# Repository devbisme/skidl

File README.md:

<div align="center">
  
</div>

**Never use a lousy schematic editor again!**

SKiDL is a Python package that lets you describe electronic circuits using code instead of schematic editors. Write your circuit as a Python program, and SKiDL outputs a netlist for PCB layout tools. It's "infrastructure as code" for electronics.

* Free software: MIT license
* Documentation: http://devbisme.github.io/skidl
* User Forum: https://github.com/devbisme/skidl/discussions

## Why SKiDL?

**Text-Based Circuit Design** `git`, `diff`, branching, and code review work on it like any other source.

**Compact & Powerful**: Describe complex circuits in a fraction of the space. No more tracing signals across multi-page schematics.

**Hierarchical Design**: Mix linear, hierarchical, and modular design approaches as needed.

**Reusable Design**: Share circuit modules on PyPI and GitHub. Create parametric "smart" circuits that adapt based on requirements.

**Design Automation**: Build circuits algorithmically. Generate repetitive structures, automatically size components, and create design variants programmatically.

**Electrical Rules Checking**: Catch common mistakes like unconnected pins, drive conflicts, and power connection errors.

**One Description, Many Outputs** Generate netlists, XML BOMs, DOT graphs, or a placed-and-routed schematic — as editable KiCad files or as static, hyperlinked SVG (KiCad 6–10) — from the same source. KiCad today; other backends can be added.

**Python Ecosystem**: Leverage Python's vast ecosystem for simulation, analysis, documentation, and automation.

## Quick Example

Here's a simple voltage divider that demonstrates SKiDL's syntax:

```python
from skidl import *

# Create input & output voltages and ground reference
vin, vout, gnd = Net('VI'), Net('VO'), Net('GND')

# Create two resistors with values and footprints
r1, r2 = 2 * Part("Device", 'R', dest=TEMPLATE, footprint='Resistor_SMD.pretty:R_0805_2012Metric')
r1.value, r2.value = '1K', '500'

# Connect the circuit elements.
vin & r1 & vout & r2 & gnd

# Or connect pin-by-pin if you prefer
# vin += r1[1]
# vout += r1[2], r2[1] 
# gnd += r2[2]

# Check for errors and generate netlist
ERC()
generate_netlist(tool=KICAD10)
```

For a more complex example, here's a two-input AND gate built from discrete transistors:

```python
from skidl import *

# Create part templates
q = Part("Transistor_BJT", "Q_PNP_CBE", dest=TEMPLATE)
r = Part("Device", "R", dest=TEMPLATE)

# Create nets
gnd, vcc = Net("GND"), Net("VCC")
a, b, a_and_b = Net("A"), Net("B"), Net("A_AND_B")

# Instantiate parts
gndt = Part("power", "GND")             # Ground terminal
vcct = Part("power", "VCC")             # Power terminal
q1, q2 = q(2)                           # Two transistors
r1, r2, r3, r4, r5 = r(5, value="10K")  # Five 10K resistors

# Make connections - notice the readable topology
a & r1 & q1["B C"] & r4 & q2["B C"] & a_and_b & r5 & gnd
b & r2 & q1["B"]
q1["C"] & r3 & gnd
vcc += q1["E"], q2["E"], vcct
gnd += gndt

generate_netlist(tool=KICAD10)
```

## Advanced Features

**Hierarchical design.** Nest subcircuits to build large systems from blocks; the hierarchy carries through to the generated net lists and schematics.

**Part and net classes.** Attach design rules, manufacturing requirements, and electrical specs to sets of parts or nets.

**Smart Part Libraries**: Search parts by function, automatically assign footprints, and access any KiCad library.

**Multiple Output Formats**: Generate netlists for KiCad, XML for BOMs, or go directly to PCB layout.

**Visual Output**: Create editable KiCad schematic files or static SVG drawings of them (KiCad 6–10), or DOT graphs for documentation. Hierarchical designs become linked SVG pages you can click through.

**SPICE Integration**: Run simulations directly on your SKiDL circuits.

## Installation

```bash
pip install skidl
```

Set up KiCad library access (optional but recommended):

```bash
# Linux/Mac
export KICAD_SYMBOL_DIR="/usr/share/kicad/symbols"

# Windows  
set KICAD_SYMBOL_DIR=C:\Program Files\KiCad\share\kicad\symbols
```

## Getting Started

1. **Learn the basics**: Check out the [documentation](http://devbisme.github.io/skidl) for comprehensive tutorials
2. **Try examples**: Explore the `tests/examples/` directory in the repository
3. **Get help**: Join discussions in our [user forum](https://github.com/devbisme/skidl/discussions)
4. **Convert existing designs**: Use the `netlist_to_skidl` tool to convert KiCad designs to SKiDL

## Troubleshooting

### "No libraries found" or symbol resolution errors

SKiDL needs to know where your KiCad symbol libraries are. If `KICAD_SYMBOL_DIR` is not
set or points to the wrong path, parts won't resolve.

**Find your KiCad symbol library path:**

```bash
# Linux (package manager install)
ls /usr/share/kicad/symbols/

# Linux (Flatpak)
ls /var/lib/flatpak/app/org.kicad.KiCad/current/active/files/share/kicad/symbols/

# macOS (Homebrew)
ls /Applications/KiCad/KiCad.app/Contents/SharedSupport/symbols/

# Windows (typical)
dir "C:\Program Files\KiCad\8.0\share\kicad\symbols"
```

**Set the environment variable:**

```bash
# Linux/macOS — add to ~/.bashrc, ~/.zshrc, or ~/.zprofile
export KICAD_SYMBOL_DIR="/usr/share/kicad/symbols"

# Windows PowerShell
[System.Environment]::SetEnvironmentVariable("KICAD_SYMBOL_DIR", "C:\Program Files\KiCad\8.0\share\kicad\symbols", "User")
```

**Verify it works:**

```bash
python -c "from skidl import Part; r = Part('Device', 'R'); print(f'Found: {r.name}')"
```

### KiCad version compatibility

SKiDL supports KiCad 5 through 10. The exceptions are the two drawing outputs —
`generate_schematic()` and `generate_svg()` — which require KiCad 6 or later.
KiCad 5 uses the legacy EESCHEMA `.sch` format, which is no longer written, and its
libraries don't carry the symbol graphics the SVG renderer draws from. KiCad 5
netlists, PCBs, and XML BOMs are unaffected.

If you see parsing errors with newer KiCad library
files, make sure you're running the latest version of SKiDL:

```bash
pip install --upgrade skidl
```

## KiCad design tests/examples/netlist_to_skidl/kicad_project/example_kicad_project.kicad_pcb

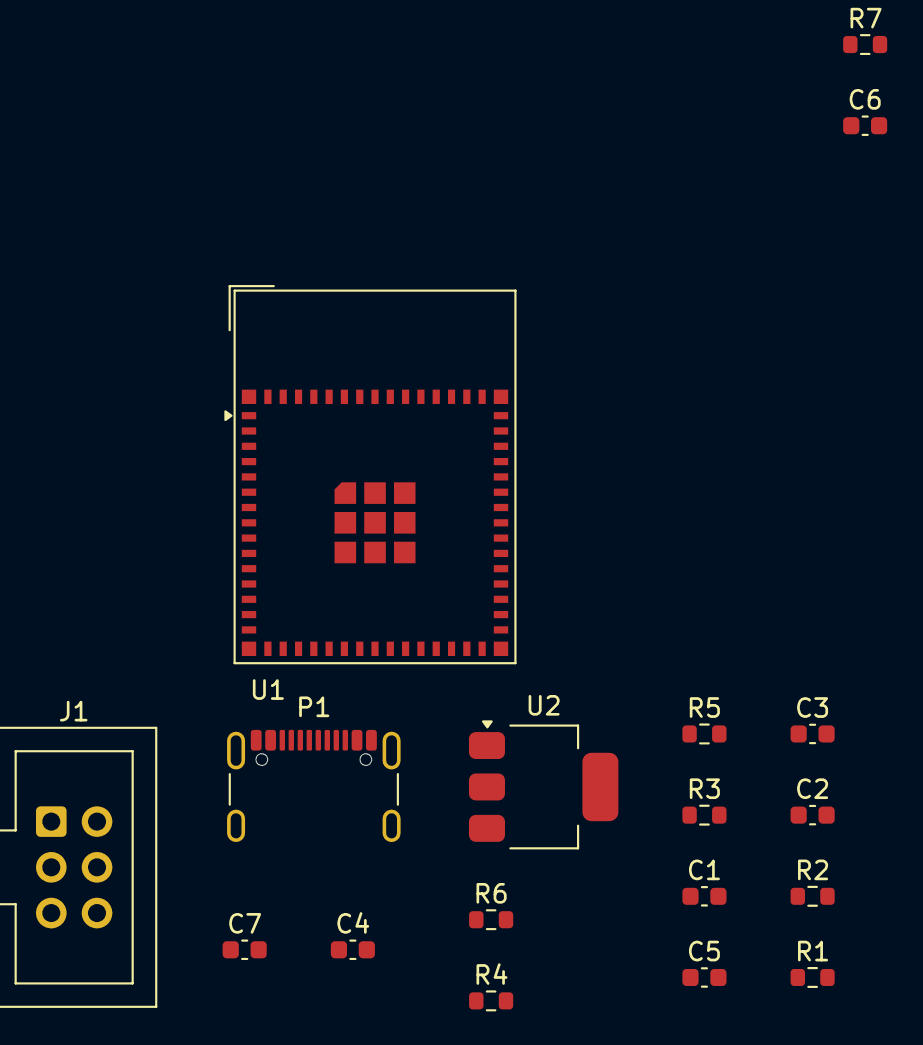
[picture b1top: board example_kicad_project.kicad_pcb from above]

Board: 2 copper layers, 18 parts (0 on the bottom side), 13 nets, no tracks yet.

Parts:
C1, C3, C4, C7: 10uF; C_0603_1608Metric
C2, C5, C6: 100nF; C_0603_1608Metric
J1: Conn_02x03_Odd_Even; IDC-Header_2x03_P2.54mm_Vertical
P1: USB_C_Plug_USB2.0; USB_C_Receptacle_GCT_USB4105-xx-A_16P_TopMnt_Horizontal
R1, R4, R5: 1k; R_0603_1608Metric
R2, R3, R6: 2k; R_0603_1608Metric
R7: 5.1K; R_0603_1608Metric
U1: ESP32-S3-MINI-1; ESP32-S2-MINI-1
U2: NCP1117-3.3_SOT223; SOT-223-3_TabPin2

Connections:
3v3_monitor: C5.1, R4.1, R6.2, U1.6
5v_monitor: C6.1, R3.2, R5.1, U1.7
+3V3: C1.1, C3.1, J1.2, R2.1, R6.1, U1.3, U2.2
+5V: C4.1, C7.1, P1.A4, P1.A9, P1.B4, P1.B9, R3.1, U2.3
D+: P1.A6, U1.24
D-: P1.A7, U1.23
GND: C1.2, C2.2, C3.2, C4.2, C5.2, C6.2, C7.2, J1.4, P1.A1, P1.A12, P1.B1, P1.B12, P1.S1, R1.2, R4.2, R5.2, R7.2, U1.1, U1.2, U1.42, U1.43, U1.46, U1.47, U1.48, U1.49, U1.50, U1.51, U1.52, U1.53, U1.54, U1.55, U1.56, U1.57, U1.58, U1.59, U1.60, U1.61, U1.62, U1.63, U1.64, U1.65, U2.1
unnamed: P1.A5, R7.1
esp32s3mini1/EN: J1.1, U1.45
esp32s3mini1/HW_VER: C2.1, R1.1, R2.2, U1.5
esp32s3mini1/IO0: J1.6, U1.4
esp32s3mini1/RX: J1.5, U1.40
esp32s3mini1/TX: J1.3, U1.39

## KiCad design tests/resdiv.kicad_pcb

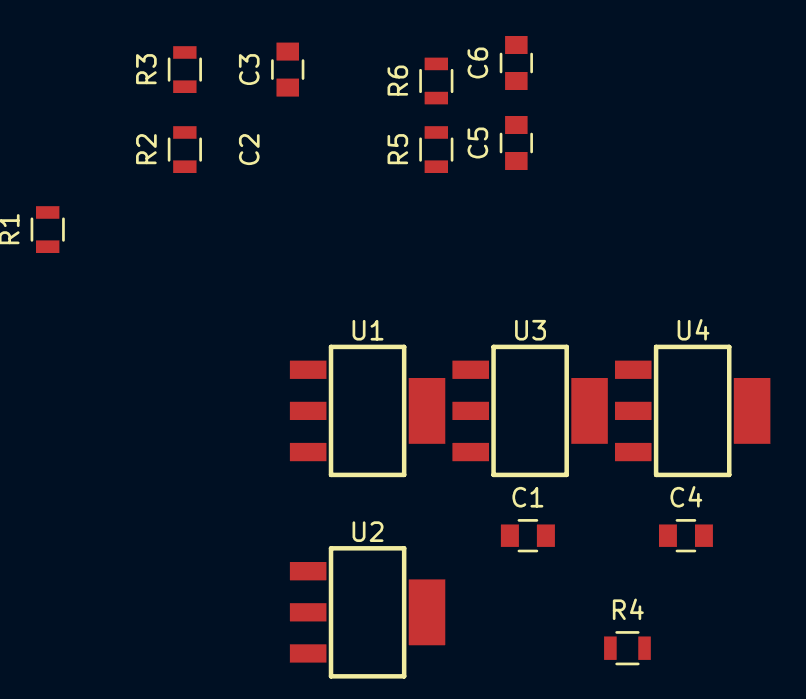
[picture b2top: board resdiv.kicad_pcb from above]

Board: 2 copper layers, 16 parts (0 on the bottom side), 4 nets, no tracks yet.

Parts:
C1, C4: C-NONPOL; C_0805
C2, C5: 1uF; C_0805
C3, C6: 2uF; C_0805
R1, R4: R; R_0805
R2, R5: 1K6; R_0805
R3, R6: 500K3; R_0805
U1, U2, U3, U4: NCV1117; SOT-223

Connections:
A: C2.1, R2.1, U1.3, U2.3
B: C2.2, C3.1, C5.1, R2.2, R3.1, R5.1, U1.2, U2.2, U3.3, U4.3
GND: C3.2, C6.2, R3.2, R6.2, U1.1, U2.1, U3.1, U4.1
unnamed: C5.2, C6.1, R5.2, R6.1, U3.2, U4.2

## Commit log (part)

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2025-06-01 Use a stack for managing the entrance and exit of Circuit objects called within another Circuit object.
2025-06-03 SchNode is no longer a subclass of Node. They should be kept separate at this point.
2025-06-08 Enhance get_unique_name function to handle numeric suffixes more effectively by appending underscores and optimizing name conflict resolution.
2025-06-08 Removed completed TODO comment for reworking get_unique_name function
2025-06-08 Enhance get_skidl_trace function documentation and improve call stack filtering of calls to SKiDL package functions.
2025-06-08 Removed old code that was commented out.
2025-06-14 Added import of setup_function and teardown_function otherwise initialization and termination of the tests won't be done.
2025-06-21 SKiDL no longer runs under Python 3.7 because it uses Simp_sexp.
2025-06-21 bare_warnings and bare_errors are now added to the total warning and error counts.
2025-06-21 Add tag management to SkidlBaseObj so it would apply to nodes and parts.
2025-06-21 Cleaned-up Node handling including checking Node tags.
2025-06-21 Import HIER_SEP from schbaseobj.py instead of circuit.py.
2025-06-21 Remove tag handling from Part since that is now provided in SkidlBaseObj.
2025-06-22 Add support for tracking absolute or relative source file paths in gen_netlist functions
2025-06-23 Refactor gen_sheetpath and gen_sheetpath_tstamp to create their outputs with the same format as KiCad.
2025-06-30 Replace dependency on kinparse with simp_sexp.
2025-06-30 Updated example projected to KiCad 9.
2025-07-02 Replaced many .format() calls with f-strings.
2025-07-03 Add examples and test data to the repo.
2025-07-05 Add testing with Python 3.6.
2025-07-13 Enhance net class management in SKiDL
    - Updated the netclass.py module to provide comprehensive net class management features, including detailed documentation, examples, and improved functionality for defining and managing net classes.
    - Introduced a new NetClassList class for managing multiple NetClass objects, supporting automatic deduplication and circuit-aware lookups.
    - Modified the NetClass constructor to ensure default priority assignment and improved error handling.
    - Updated unit tests to validate the new net class merging behavior and ensure correct propagation of net class attributes across merged nets.
2025-07-13 Add priority sorting for elements in a NetClass and corresponding unit test
2025-07-13 Add netclass handling to netlist generation and default netclass assignment
2025-07-13 Add netclass handling to netlist generation for KiCad 8 and assign Default netclass to all nets
2025-07-14 Add PartClass and PartClassList for managing part classes in Part objects
2025-07-15 Added AI-generated tests of the Circuit class.
2025-07-15 Add NCNet class import for enhanced net management
2025-07-19 Remove NCNet import from __init__.py because normal SKiDL users don't need it.
2025-07-20 Insert part classes into netlist output.
2025-07-20 Replace Group with SubCircuit which now can serve as a class and a decorator for creating hierarchical circuits. Retain Group for backward compatibility.
2025-07-20 - Correct __all__. - Add documentation.
2025-07-24 Rename 'i_expression' and 'v_expression' to 'current_expression' and 'voltage_expression' in the PySpice keyword translation table.
2025-07-28 Give notice along with corrective action if SPICE simulation cannot be performed.
2025-08-03 Add tests for net classes.
2025-08-03 Refactor add_netclass and add_partclass methods to accept multiple classes and add property accessors for netclasses and partclasses.
2025-08-03 Preliminary update of HISTORY for version 2.1.0
2025-08-03 Refactor part copying logic to handle iterable attributes correctly and remove unnecessary part class list copying.
2025-08-04 Fix copy method in Parameters class to return a Parameters instance instead of a dict
2025-08-04 Add hiernodes property to return the chain of hierarchical nodes for a SKiDL object.
2025-08-04 Add test for hierarchical part classes.
2025-08-05 Remove UTF-8 encoding setup for Python 2 compatibility
2025-08-07 Add test for hierarchical net classes.
2025-08-09 Update return type in SubCircuit class documentation to reflect Node object
2025-08-10 Merged subcircuit handling from subcircuit.py into Node objects.
2025-08-10 Update check for power to support PartClassList in Net objects.
2025-08-10 Add AI-generated unit tests for PartClass, PartClassList, NetClass, and NetClassList functionality
2025-08-14 - Replaced DesignClass with NetClassList and PartClassList. - Fixed hierarchical propagation of net and part classes.
2025-08-14 Refactor tests to use updated PartClass and NetClass implementations.
2025-08-14 Updated history.
2025-08-16 Fix formatting in Net class docstring for clarity
2025-08-16 - Link buses to the nodes where they were instantiated. - Link nodes to the buses where they were instantiated.
2025-08-16 Add tests for net classes in buses.
2025-08-16 Added instructions for creating llms.txt file.
2025-08-17 Refactor file path search for footprint library table retrieval.
2025-08-17 Add interactive mode support to scriptinfo function so it returns "skidl_REPL" as the script name.
2025-08-20 When generating a unique name for a name ending with a digit, append an underscore before searching the heap so previous generated names will be found.
2025-08-21 Remove "_lib" from backup library name assignment and use script name directly with appended "_sklib.py".
2025-08-23 Improve Bus and Net copy method to include circuit and name attributes.
2025-08-23 Replaced hierarchical_name with hiername in Part class.
2025-08-24 Moved hiertuple, hierpath, etc. from SkidlBaseObj to Part and Node classes.
2025-08-28 - Replace hiername with hiertuple. - Add hiertuple property to Part and PartUnit.
2025-08-28 Update xfail annotations to include PlacementFailure for schematic generation tests
2025-08-28 Add missing libraries for testing schematic geneation under KiCad 5.
2025-08-29 Add generate_dot function to SKiDL module and export it in __all__
2025-08-29 Remove unused schematic example files for and gate and landing example
2025-08-30 Update default tool selection to KICAD9 in pytest setup_function.
2025-08-30 Add AI-generated tests based on examples from landing.md documentation.
2025-08-30 Replaced README.rst file with README.md markdown file.
2025-08-30 Bump version to 2.1.0 and update release date
2025-08-30 Added llms files generated by llms-txt.io.
2025-08-31 Converted Restructured text files to Markdown.
2025-08-31 Rewrite of README.
2025-08-31 Added blog posts on 2.1.0 release and SKiDL cheatsheet.
2025-09-01 Combined testing for all Python versions, KiCad versions, SPICE, and schematics into a single testenv.
2025-09-01 Rebuilt docs to include corrected cheatsheet.
2025-09-01 Fixed link to cheatsheet in blog post preview.
2025-09-04 Removed 'spice' from the envlist in tox.ini
2025-09-04 Correct XSPICE unit test.
2025-09-07 Add os.path.abspath() to expand_path() utility.
2025-09-07 Add __iter__ to SchLib to enable iterating over the parts in a library.
2025-09-10 - SKiDL configuration now uses standard locations for storing .skidlcfg. - Configuration process now creates a storage directory for pickled part libraries and the part search database. - Use collect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
2025-09-11 - Updated configuration of unit tests to use a .skidlcfg file. - Updated test of part search to account for new database search technique.
2025-09-13 Added skidl-part-search command-line utility.
2025-09-14 Corrected version number.
2025-09-16 Reset file name assignment to the base name of the library. Complete file path is now stored in the filepath attribute.
2025-09-20 Add interactive search mode with command history support.
2025-09-20 - Enhance search output with colored number of results message. - Correct readline history bindings.
2025-09-20 Improve interactive browsing experience with enhanced part navigation and display features
2025-09-27 Separated pin handling in Part into a mixin class.
2025-09-28 - Add create_pins() for adding pins to Parts and SubCircuits. - Add erc_desc() to SubCircuit for reporting ERC warnings/errors. - Add PinMixin to SubCircuit class. - Move match_pin_regex property fro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
2025-09-28 Remove --pdb option from pytest command in tox.ini
2025-10-04 Bus indexing using aliases is now supported.
2025-10-05 Add test for nested subcircuits using SubCircuit subclass and create_pins().
2025-10-07 Alternate pin names in KiCad symbols are now added as aliases to Pin objects in Parts.
2025-10-14 Cast NetPinList to list for standard indexing in test_pin_number_access.
2025-10-14 Skip test if STM32 part library is missing.
2025-10-28 Added test for pin names containing spaces.
2025-10-29 Implement initialize and finalize methods to streamline the creation of SubCircuits.
2025-11-06 Fix examples in split_unquoted docstring.
2025-11-10 Added further examples.
2025-11-10 Rebuilt online user-facing documentation.
2025-11-11 Added blog post announcing release of version 2.2.0.
2025-11-12 Refactor netlist generation to support file-like objects and add test for StringIO output.
2025-11-26 Summary of Changes to mixins.py The changes fix a critical bug in the rmv_pins() method:
    Three main issues were resolved:
    Variable name error: del pins[i] → del self.pins[i] (the variable pins didn't exist)
    Logic error: Changed from in operator to exact equality (==)
    Before: pin.num in pin_ids would match incorrectly
    After: pin.num == pin_id checks for exact matches
    Loop structure: Reorganized to iterate over pin_ids first, then search through pins for better predictability
2025-11-26 update docs
2025-12-06 Pin class now updates aliases when a pin name or number is changed.
2025-12-06 Convert identifiers used to search for pins into strings since pin numbers and names are stored as strings.
2025-12-13 Updated history to list new fixes.
2025-12-13 Bumped release and updated docs.
2025-12-26 Release announcement blog post
2026-04-21 Removed a SPICE pin alias that might get confused with another parameter.
2026-04-21 Simplified and corrected SPICE voltage regulator example.
2026-04-22 Refactor SPICE test to remove unused code and correct pin mapping for voltage sources
2026-04-24 pyspice_lib is already instantiated at import time, so there's no need to reload it.
2026-04-24 Correct syntax errors and update plot titles.
2026-04-24 Update plot title for current-controlled switch inverter test
2026-04-30 Add circuit example for netlist generation with SPICE templates.
2026-05-11 Fix flattening logic to ensure slack is positive before processing child instances
2026-05-12 Use node_to_sexp_schematic() to create schematic files for all hierarchy levels including the top-level root.
2026-05-13 Modify node_to_sexp_schematic so part/power symbols in flattened sheets are collected and returned to allow creation of complete symbol libraries in the parent sheet.
2026-05-14 Fixed missing power symbols (??) in schematics.
2026-05-14 Corrected flattening error where parent node complexity was not being increased for each child that was merged.
2026-05-14 Updated tests/examples for modified KiCad 9 schematic generator.
2026-05-23 Add device name and reference preservation
2026-05-25 fix(gensch): 移除flatten参数
2026-05-25 feat(sch-mcu):添加mcu模块，但是标签过多
2026-05-26 fix(label): 已有导线时跳过重复的 global_label
2026-05-26 fix(power): 统一 power net 识别与 KiCad power symbol 外形映射
2026-05-26 fix(mcu)：修复短路问题
2026-05-26 fix(mcu): 修复匿名信号网被 stub 导致标签漂浮
2026-05-27 fix(label):修复NetTerminal 和 stub 标签重复导出，导致同一网络出现多个标签
2026-05-28 fix(mcu)：添加mcu左右两侧wire不连接原则
2026-05-28 fix MCU decoupling ground trunk layout
2026-05-30 feat(jlc):新增嘉立创ENET原生转换入口
2026-06-08 Commit test with merge conflicts fixed.
